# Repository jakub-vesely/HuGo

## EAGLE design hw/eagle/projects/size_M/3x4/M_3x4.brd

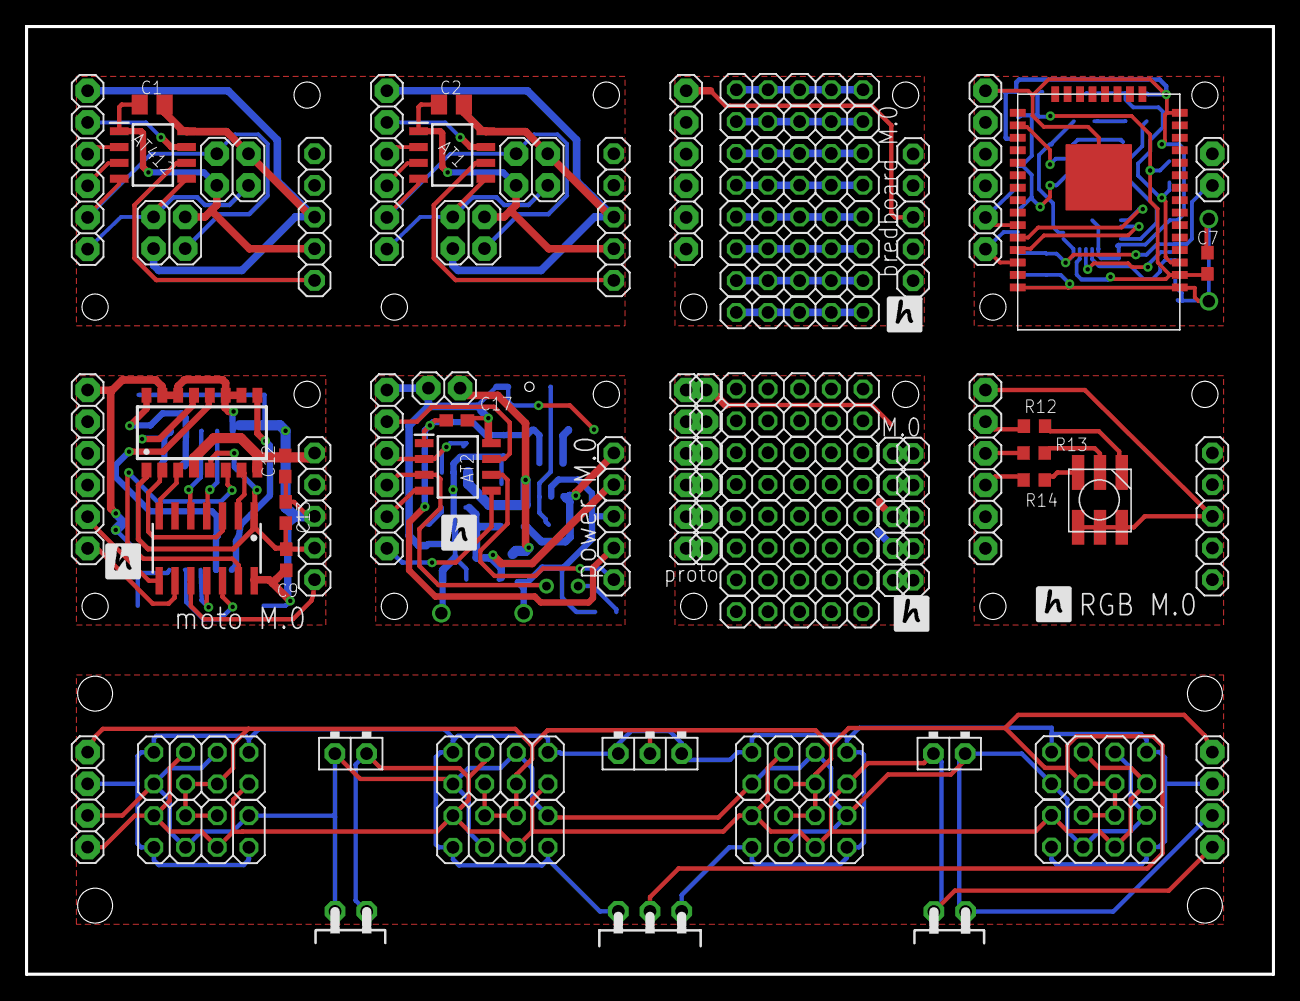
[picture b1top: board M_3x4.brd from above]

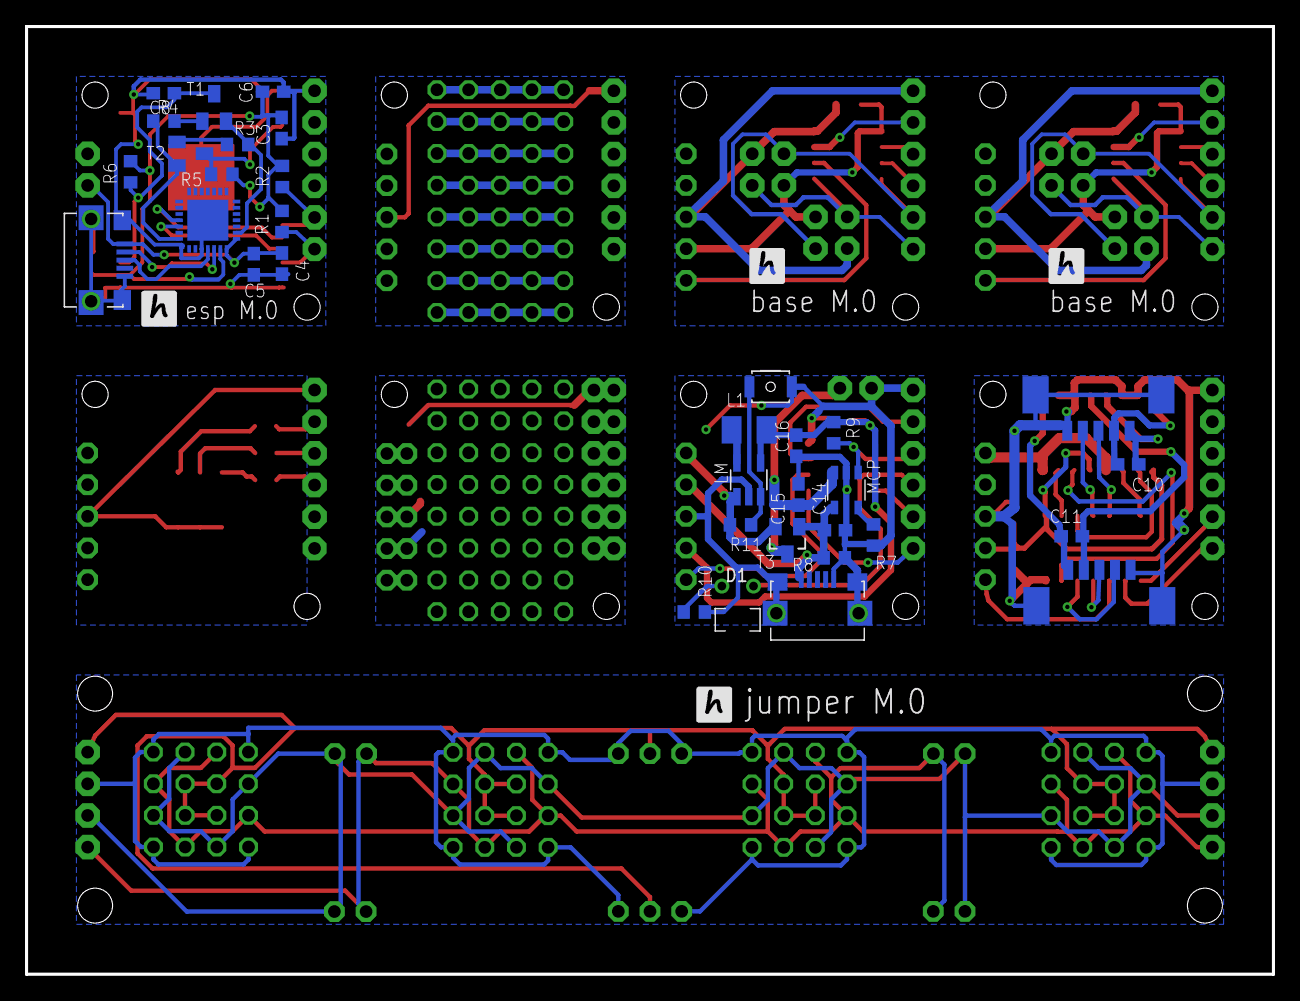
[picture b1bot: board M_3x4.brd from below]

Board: 2 copper layers, 100.0 x 76.0 mm, 106 parts (34 on the bottom side), 92 nets.

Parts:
AT1, AT2, AT412: AT412; SOIC127P600X175-8N
C1, C2: 100n; C0805K
C3, C4, C6, C9, C10, C11, C17: 100n; C0603
C5, C16: 10u; C0603
C7: 0.1F; C0603
C8: 2u2; C0603
C12, C13, C14, C15: 4u7; C0603
D1: LED1.8
IC1: CP2102; MLP28
IC2: AT414; SO14
JP1, JP2, JP9, JP10, JP13, JP15, JP17, JP19, JP21: 1X06
JP3, JP4, JP6, JP7: 2X02
JP5, JP8, JP11, JP14, JP16, JP18, JP20, JP22: 1X05
JP12: 1X02
JP23, JP25, JP26, JP27, JP28, JP29, JP33, JP34: 2X04
JP24, JP35: 1X02/90F
JP30, JP36: 1X02/90
JP31: 1X03/90
JP32: 1X03/90F
JP37, JP38: 1X04
L1: 2u2; L3230M
LIPOL: 1X02
LM: TC; SOT32-5
MCP: MCP; SOT23-5
MX1: MX1508; SOP16
R1, R2, R10: 2k2; R0603
R3, R4, R5, R6: 12k; R0603
R7: 22k; R0603
R8, R9, R11: 100k; R0603
R12, R13, R14: 330; R0603
RESET: BYTTON-B3U; BUTTON-B3U
T1, T2: SOT23-BEC
T3: FDV; SOT23
U$1, U$2, U$3, U$4, U$5, U$6, U$7, U$8, U$11, U$12, U$13, U$14, U$15, U$16, U$17, U$18: PINHD-1X5_AUTO; 1X5_AUTO
U$9: TTGO-MICRO-32
U$10: A1250WR
U$19: RGB_WW-FCE50TC-Q1
USB, USB1: MICRO-USB
X22: A1250WR

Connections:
FOTO1: IC2.5, U$10.3
FOTO2: IC2.12, X22.4
GND: AT1.8, AT412.8, C1.2, C2.2, JP1.6, JP2.6, JP3.4, JP4.1, JP5.3, JP6.4, JP7.1, JP8.3
GND1: JP9.6, JP11.3
GND2: C3.2, C4.1, C5.1, C6.2, C7.2, C8.2, IC1.3, IC1.EXP, IC1.M, JP10.6, U$9.GND1, U$9.GND2, U$9.GND3, U$9.GND4, USB.GND, USB.GND1, USB.GND2, USB.GND3, USB.GND4, USB.P$1, USB.P$2
GND3: C9.1, C12.1, C13.1, IC2.14, JP13.6, JP14.3, MX1.10, MX1.11, MX1.14, MX1.15, U$10.5, U$10.$1, U$10.$2, X22.5, X22.$1, X22.$2
GND4: AT2.8, C14.1, C15.1, C16.1, C17.2, JP15.6, JP16.3, LIPOL.1, LM.GND, MCP.2, R7.1, R8.1, R10.1, RESET.P$2, USB1.GND, USB1.GND1, USB1.GND2, USB1.GND3, USB1.GND4, USB1.P$1, USB1.P$2
GND5: JP17.6, JP18.3, JP19.6, JP20.3
GND6: JP21.6, JP22.3, U$19.4, U$19.5, U$19.6
GND7: JP23.1, JP23.7, JP25.2, JP25.8, JP26.1, JP26.7, JP27.2, JP27.8, JP28.1, JP28.7, JP29.2, JP29.8, JP31.1, JP31.3, JP32.1, JP32.3, JP33.1, JP33.7, JP34.2, JP34.8, JP37.2, JP38.3
INA1: IC2.3, MX1.2
INA2: IC2.13, MX1.6
INB1: IC2.7, MX1.3
INB2: IC2.2, MX1.7
LED1: IC2.4, U$10.4
LED2: IC2.11, X22.3
M1: C10.2, MX1.13, U$10.1
M2: C10.1, MX1.16, U$10.2
M3: C11.2, MX1.9, X22.1
M4: C11.1, MX1.12, X22.2
M_SRC: C12.2, JP14.1, MX1.4, MX1.8
unnamed: U$1.1, U$1.2, U$1.3, U$1.4, U$1.5
unnamed: U$2.1, U$2.2, U$2.3, U$2.4, U$2.5
unnamed: U$3.1, U$3.2, U$3.3, U$3.4, U$3.5
unnamed: U$4.1, U$4.2, U$4.3, U$4.4, U$4.5
unnamed: U$5.1, U$5.2, U$5.3, U$5.4, U$5.5
unnamed: U$6.1, U$6.2, U$6.3, U$6.4, U$6.5
unnamed: U$7.1, U$7.2, U$7.3, U$7.4, U$7.5
unnamed: U$8.1, U$8.2, U$8.3, U$8.4, U$8.5
unnamed: IC1.5, USB.D-
unnamed: IC1.4, USB.D+
unnamed: IC1.25, U$9.RXD0
unnamed: IC1.26, U$9.TXD0
unnamed: R4.2, T1.B
unnamed: R3.2, T2.B
unnamed: IC1.9, R3.1, T1.E
unnamed: IC1.28, R4.1, T2.E
unnamed: R5.1, T2.C, U$9.IO0
unnamed: C8.1, R6.2, T1.C, U$9.EN
unnamed: IC2.9, JP13.1
unnamed: IC2.8, JP13.2
unnamed: IC2.10, JP14.5
unnamed: C15.2, LIPOL.2, MCP.3, T3.D
unnamed: C14.2, JP16.2, MCP.4, R8.2, T3.G, USB1.VUSB
unnamed: MCP.5, R7.2
unnamed: JP16.1, LM.VIN, R11.1, T3.S
unnamed: D1.K, R10.2
unnamed: LM.SHDN, R11.2, RESET.P$1
unnamed: L1.1, LM.VOUT
unnamed: JP17.5, JP19.5
unnamed: JP17.4, JP19.4
unnamed: JP17.3, JP19.3
unnamed: JP17.2, JP19.2
unnamed: JP17.1, JP19.1
unnamed: JP18.5, JP20.5
unnamed: JP18.2, JP20.2
unnamed: JP18.1, JP20.1
unnamed: R13.2, U$19.2
unnamed: R12.2, U$19.1
unnamed: R14.2, U$19.3
unnamed: JP21.5, R12.1
unnamed: JP21.4, R13.1
unnamed: JP21.3, R14.1
PA1: AT1.7, JP1.5
PA2: AT1.2, JP1.4
PA3: AT412.7, JP2.5
PA4: AT1.3, JP1.3
PA5: AT2.7, JP15.5
PA6: AT412.2, JP2.4
PA7: AT412.3, JP2.3
PA8: AT2.2, JP15.4, MCP.1, R9.2
PA9: AT2.3, D1.A, JP15.3
SCL: AT412.5, JP2.1, JP3.3, JP4.2
SCL1: AT1.5, JP1.1, JP6.3, JP7.2
SCL2: JP10.1, R1.1, U$9.IO22
SCL3: AT2.5, JP15.1
SCL4: JP23.2, JP23.5, JP24.1, JP25.4, JP25.7, JP26.2, JP26.5, JP27.4, JP27.7, JP28.2, JP28.5, JP29.4, JP29.7, JP30.2, JP33.2, JP33.5, JP34.4, JP34.7, JP35.2, JP36.1, JP37.4, JP38.1
SDA: AT412.4, JP2.2, JP3.2, JP4.3
SDA1: AT1.4, JP1.2, JP6.2, JP7.3
SDA2: JP10.2, R2.1, U$9.IO21
SDA3: AT2.4, JP15.2
SDA4: JP23.3, JP23.8, JP24.2, JP25.1, JP25.6, JP26.3, JP26.8, JP27.1, JP27.6, JP28.3, JP28.8, JP29.1, JP29.6, JP30.1, JP33.3, JP33.8, JP34.1, JP34.6, JP35.1, JP36.2, JP37.3, JP38.2
UPDI: AT412.6, JP5.5
UPDI1: AT1.6, JP8.5
UPDI2: AT2.6, JP16.5
VCC: C9.2, C13.2, IC2.1, JP14.4, MX1.1, MX1.5
VCC1: JP23.4, JP23.6, JP25.3, JP25.5, JP26.4, JP26.6, JP27.3, JP27.5, JP28.4, JP28.6, JP29.3, JP29.5, JP31.2, JP32.2, JP33.4, JP33.6, JP34.3, JP34.5, JP37.1, JP38.4
VDD: AT1.1, AT412.1, C1.1, C2.1, JP3.1, JP4.4, JP5.4, JP6.1, JP7.4, JP8.4
VDD2: C3.1, C6.1, C7.1, IC1.6, R1.2, R2.2, R5.2, R6.1, U$9.3V3
VDD3: AT2.1, C16.2, C17.1, JP16.4, L1.2, LM.BP, R9.1
VDD4: JP18.4, JP20.4
VUSB: C4.2, C5.2, IC1.7, IC1.8, JP12.2, USB.VUSB

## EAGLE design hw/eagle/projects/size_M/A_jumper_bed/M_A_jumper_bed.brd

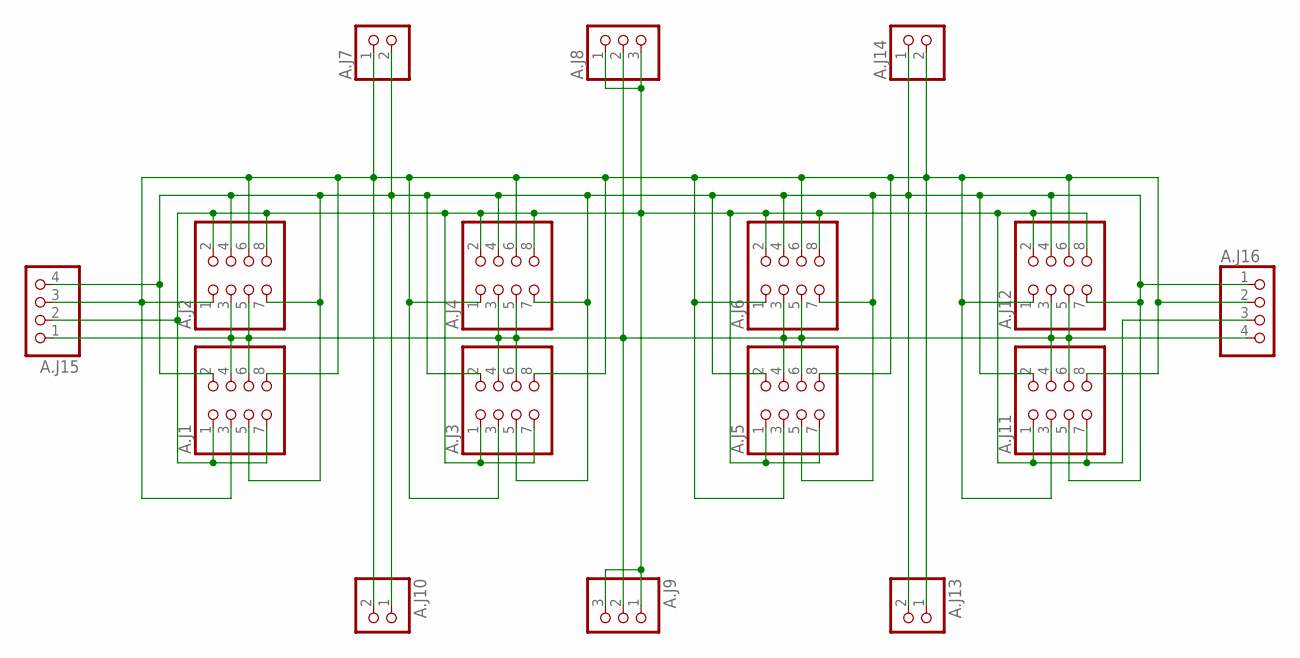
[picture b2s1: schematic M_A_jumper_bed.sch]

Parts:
A.J1, A.J2, A.J3, A.J4, A.J5, A.J6, A.J11, A.J12: PINHD-2X4; 2X04
A.J7, A.J14: PINHD-1X2/90; 1X02/90
A.J8: PINHD-1X3/90; 1X03/90
A.J9: PINHD-1X31X03/90F; 1X03/90F
A.J10, A.J13: PINHD-1X21X02/90F; 1X02/90F
A.J15, A.J16: PINHD-1X4; 1X04

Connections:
GND: A.J1.1, A.J1.7, A.J2.2, A.J2.8, A.J3.1, A.J3.7, A.J4.2, A.J4.8, A.J5.1, A.J5.7, A.J6.2, A.J6.8, A.J8.1, A.J8.3, A.J9.1, A.J9.3, A.J11.1, A.J11.7, A.J12.2, A.J12.8, A.J15.2, A.J16.3
SCL: A.J1.2, A.J1.5, A.J2.4, A.J2.7, A.J3.2, A.J3.5, A.J4.4, A.J4.7, A.J5.2, A.J5.5, A.J6.4, A.J6.7, A.J7.2, A.J10.1, A.J11.2, A.J11.5, A.J12.4, A.J12.7, A.J13.2, A.J14.1, A.J15.4, A.J16.1
SDA: A.J1.3, A.J1.8, A.J2.1, A.J2.6, A.J3.3, A.J3.8, A.J4.1, A.J4.6, A.J5.3, A.J5.8, A.J6.1, A.J6.6, A.J7.1, A.J10.2, A.J11.3, A.J11.8, A.J12.1, A.J12.6, A.J13.1, A.J14.2, A.J15.3, A.J16.2
VCC: A.J1.4, A.J1.6, A.J2.3, A.J2.5, A.J3.4, A.J3.6, A.J4.3, A.J4.5, A.J5.4, A.J5.6, A.J6.3, A.J6.5, A.J8.2, A.J9.2, A.J11.4, A.J11.6, A.J12.3, A.J12.5, A.J15.1, A.J16.4

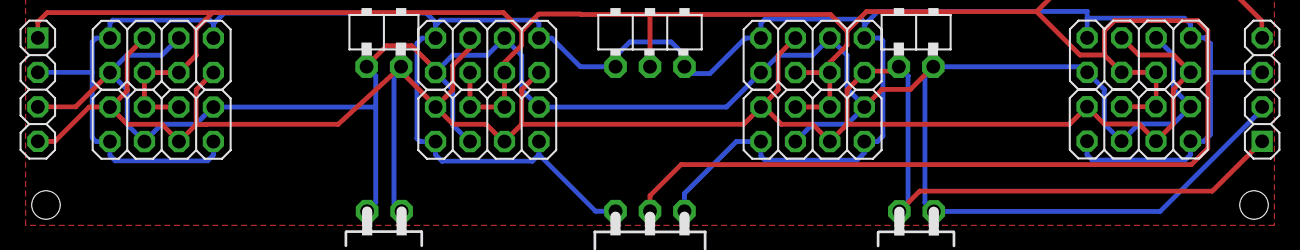
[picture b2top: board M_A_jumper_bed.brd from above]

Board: 2 copper layers, 16 parts (0 on the bottom side), 4 nets.

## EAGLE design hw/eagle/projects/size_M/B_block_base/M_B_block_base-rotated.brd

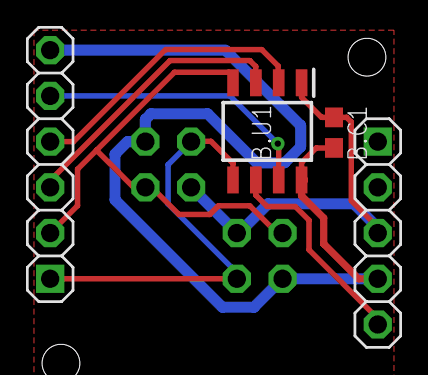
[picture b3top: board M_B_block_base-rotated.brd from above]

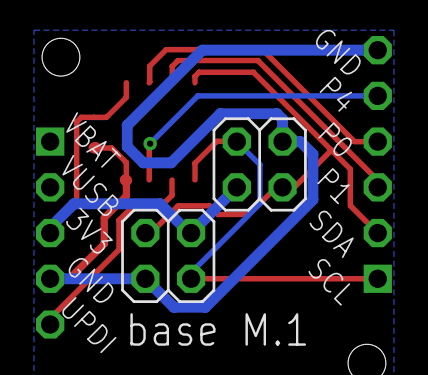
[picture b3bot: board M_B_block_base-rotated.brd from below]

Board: 2 copper layers, 6 parts (2 on the bottom side), 8 nets.

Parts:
B.C1: 100n; C0603
B.J2: 1X06
B.J4: 2X02
B.J5: 1X05
B.U1: AT412; SOIC127P600X175-8N
JB3: 2X02

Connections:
3V3: B.C1.1, B.J4.4, B.J5.3, B.U1.1, JB3.1
GND: B.C1.2, B.J2.6, B.J4.1, B.J5.4, B.U1.8, JB3.4
PA3: B.J2.5, B.U1.7
PA6: B.J2.4, B.U1.2
PA7: B.J2.3, B.U1.3
SCL: B.J2.1, B.J4.3, B.U1.5, JB3.2
SDA: B.J2.2, B.J4.2, B.U1.4, JB3.3
UPDI: B.J5.5, B.U1.6

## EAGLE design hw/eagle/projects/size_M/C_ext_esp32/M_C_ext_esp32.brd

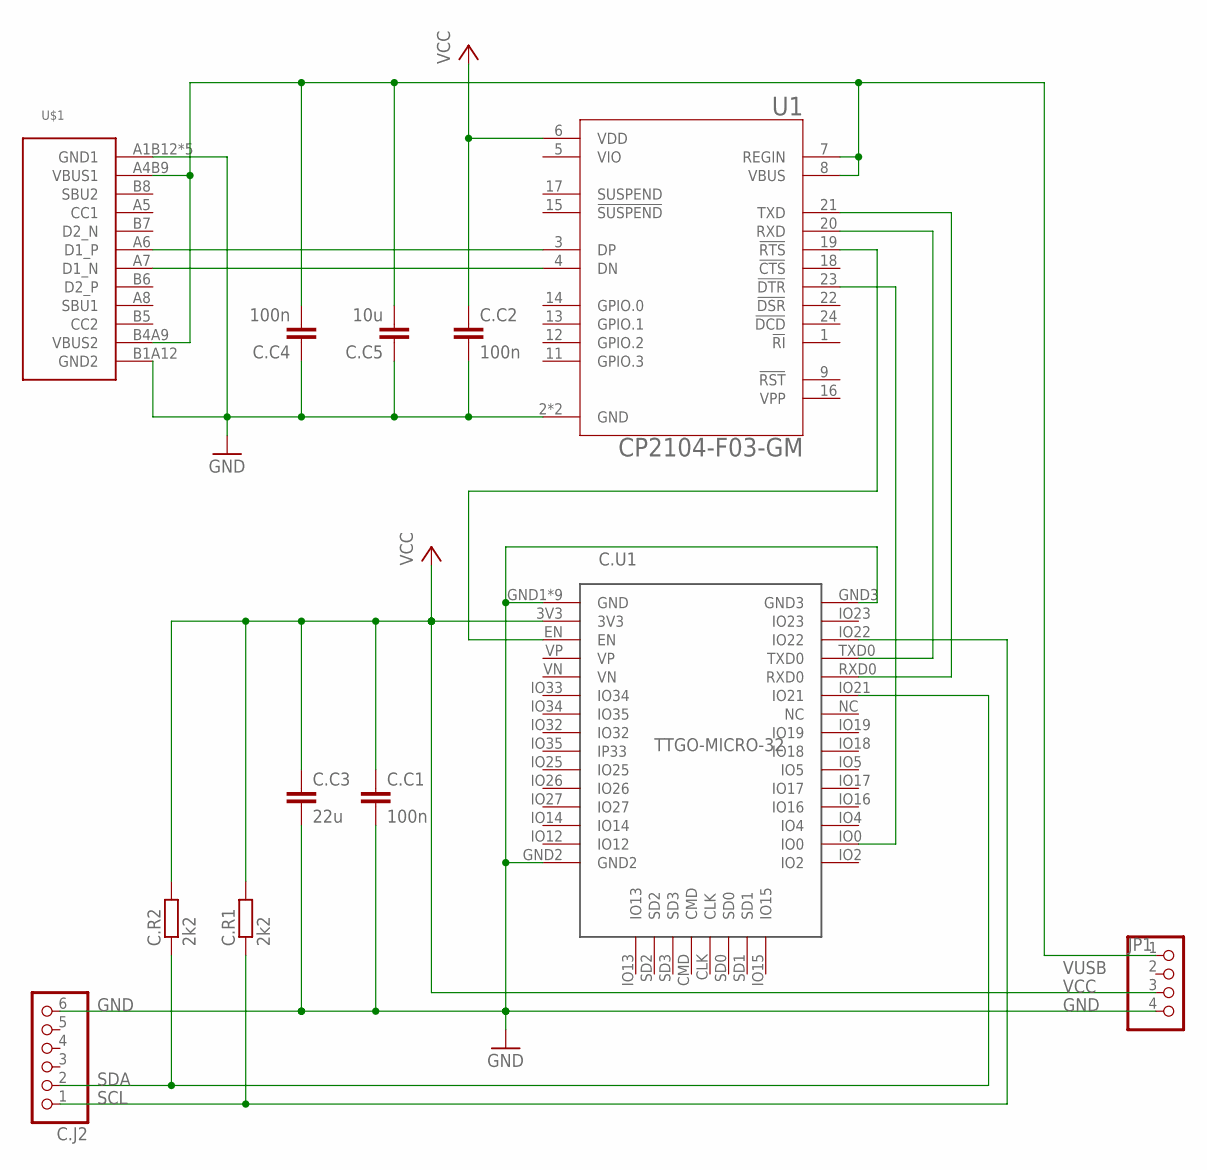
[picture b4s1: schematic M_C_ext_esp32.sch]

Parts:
C.C1, C.C2, C.C4: 100n; C0603
C.C3: 22u; C0805
C.C5: 10u; C0603
C.J2: PINHD-1X6; 1X06
C.R1, C.R2: 2k2; R0603
C.U1: TTGO-MICRO-32
JP1: PINHD-1X4; 1X04
U1: CP2104-F03-GM; QFN50P400X400X80-25N
U$1: USB-C

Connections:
GND: C.C1.2, C.C2.2, C.C3.2, C.C4.1, C.C5.1, C.J2.6, C.U1.GND1 (GND), C.U1.GND2, C.U1.GND3, C.U1.GND4 (GND), C.U1.GND5 (GND), C.U1.GND6 (GND), C.U1.GND7 (GND), C.U1.GND8 (GND), C.U1.GND9 (GND), C.U1.GND10 (GND), C.U1.GND11 (GND), JP1.4, U1.2 (GND), U1.25 (GND), U$1.A1B12 (GND1), U$1.B1A12 (GND2), U$1.SH1 (GND1), U$1.SH2 (GND1), U$1.SH3 (GND1), U$1.SH4 (GND1)
unnamed: U1.4 (DN), U$1.A7 (D1_N)
unnamed: U1.3 (DP), U$1.A6 (D1_P)
PROG: C.U1.IO0, U1.23 (!DTR)
RESET: C.U1.EN, U1.19 (!RTS)
RX: C.U1.TXD0, U1.20 (RXD)
SCL: C.J2.1, C.R1.1, C.U1.IO22
SDA: C.J2.2, C.R2.1, C.U1.IO21
TX: C.U1.RXD0, U1.21 (TXD)
VCC: C.C1.1, C.C2.1, C.C3.1, C.R1.2, C.R2.2, C.U1.3V3, JP1.3, U1.6 (VDD)
VIO: U1.5 (VIO)
VUSB: C.C4.2, C.C5.2, JP1.1, U1.7 (REGIN), U1.8 (VBUS), U$1.A4B9 (VBUS1), U$1.B4A9 (VBUS2)

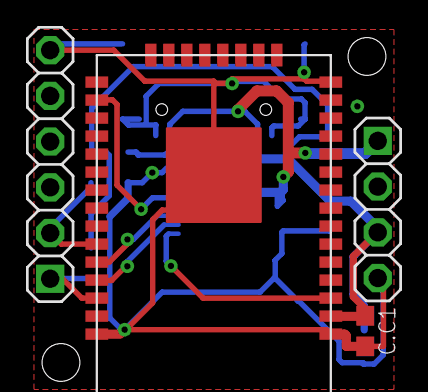
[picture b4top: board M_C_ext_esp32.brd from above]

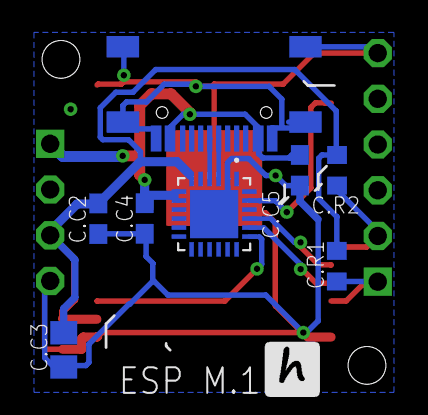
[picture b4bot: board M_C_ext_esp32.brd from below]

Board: 2 copper layers, 12 parts (8 on the bottom side), 11 nets.

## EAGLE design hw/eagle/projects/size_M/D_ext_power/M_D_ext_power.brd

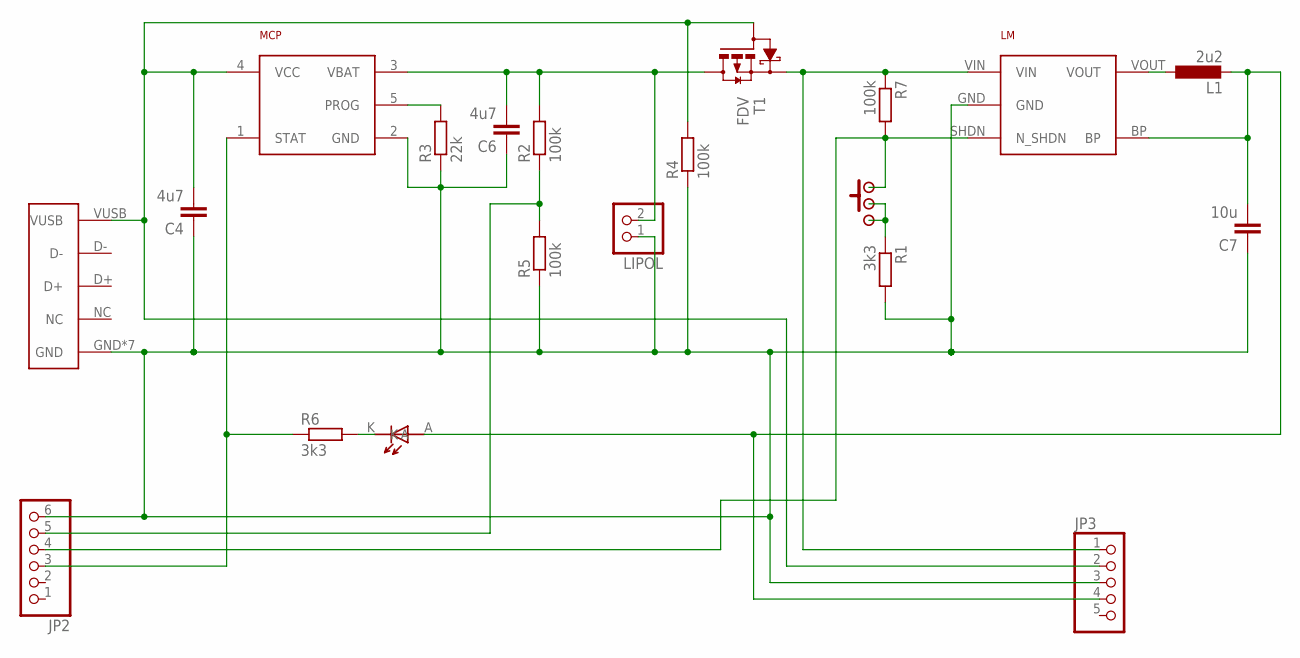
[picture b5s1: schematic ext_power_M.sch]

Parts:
C4, C6: 4u7; C0603
C7: 10u; C0603
D1: LED1.8
JP2: PINHD-1X6; 1X06
JP3: PINHD-1X5; 1X05
L1: 2u2; L3230M
LIPOL: PINHD-1X2; 1X02
LM: TC; SOT32-5
MCP: MCP; SOT23-5
ON/OFF/RESET: SWITCH
R1, R6: 3k3; R0603
R2, R4, R5, R7: 100k; R0603
R3: 22k; R0603
T1: FDV; SOT23
USB: MICRO-USB

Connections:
GND: C4.1, C6.1, C7.1, JP2.6, JP3.3, LIPOL.1, LM.GND, MCP.2 (GND), R1.2, R3.1, R4.1, R5.1, USB.GND, USB.GND1 (GND), USB.GND2 (GND), USB.GND3 (GND), USB.GND4 (GND), USB.P$1 (GND), USB.P$2 (GND)
unnamed: ON/OFF/RESET.P$2, ON/OFF/RESET.P$3, ON/OFF/RESET.P$5, R1.1
unnamed: L1.1, LM.VOUT
unnamed: D1.K, R6.2
unnamed: JP2.5, R2.1, R5.2
unnamed: C6.2, LIPOL.2, MCP.3 (VBAT), R2.2, T1.D
unnamed: C4.2, JP3.2, MCP.4 (VCC), R4.2, T1.G, USB.VUSB
unnamed: MCP.5 (PROG), R3.2
unnamed: JP3.1, LM.VIN, R7.1, T1.S
unnamed: JP2.4, LM.SHDN (N_SHDN), ON/OFF/RESET.P$1, ON/OFF/RESET.P$4, R7.2
PA7: JP2.3, MCP.1 (STAT), R6.1
VDD: C7.2, D1.A, JP3.4, L1.2, LM.BP

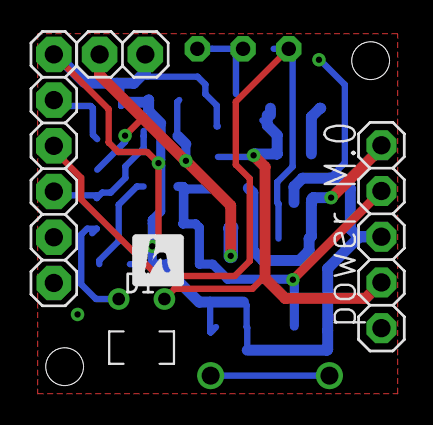
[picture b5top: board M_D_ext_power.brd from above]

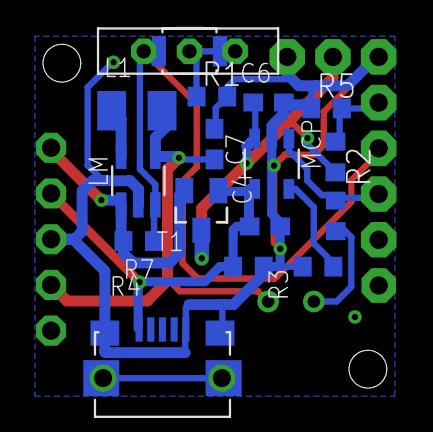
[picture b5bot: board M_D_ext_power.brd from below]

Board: 2 copper layers, 20 parts (16 on the bottom side), 12 nets.

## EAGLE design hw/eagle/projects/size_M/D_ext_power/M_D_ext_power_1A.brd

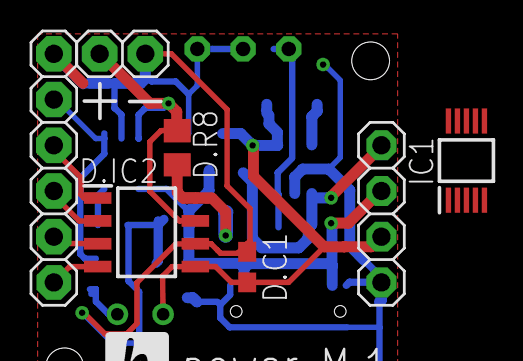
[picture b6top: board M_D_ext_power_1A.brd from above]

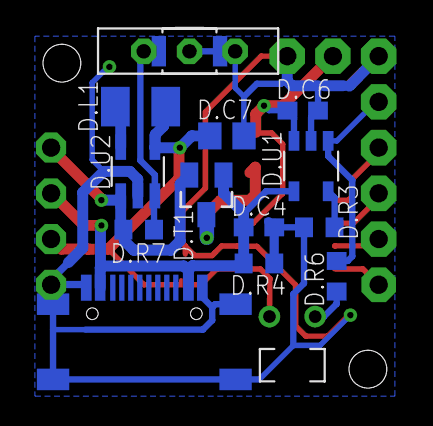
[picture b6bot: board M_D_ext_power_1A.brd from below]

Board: 2 copper layers, 21 parts (14 on the bottom side), 15 nets.

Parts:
D.C1: 100n; C0603
D.C4, D.C6: 4u7; C0603
D.C7: 22u; C0805
D.D1: LED_1.8
D.IC2: INA219AIDR; SOIC127P600X175-8N
D.J2: 1X06
D.J3: 1X04
D.L1: 2u2; L3230M
D.LIPOL: 1X02
D.ON/OFF/RESET: SWITCH
D.R3: 12k; R0603
D.R4, D.R7: 100k; R0603
D.R6: 2k2; R0603
D.R8: 0.1; R0805
D.T1: FDV; SOT23
D.U1: MCP; SOT23-5
D.U2: TC; SOT32-5
IC1: MCP73833-AMI_UN; SOP50P490X110-10N
U$1: USB-C

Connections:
GND: D.C1.1, D.C4.1, D.C6.1, D.C7.1, D.IC2.6, D.J2.6, D.J3.4, D.LIPOL.1, D.ON/OFF/RESET.P$2, D.ON/OFF/RESET.P$3, D.ON/OFF/RESET.P$5, D.R3.1, D.R4.1, D.U1.2, D.U2.GND, U$1.A1B12, U$1.B1A12, U$1.SH1, U$1.SH2, U$1.SH3, U$1.SH4
unnamed: D.IC2.1, D.J2.4
unnamed: D.L1.1, D.U2.VOUT
unnamed: D.D1.1, D.R6.2
unnamed: D.ON/OFF/RESET.P$1, D.ON/OFF/RESET.P$4, D.R7.2, D.U2.SHDN
unnamed: D.IC2.4, D.J2.1
unnamed: D.IC2.3, D.J2.2
unnamed: D.IC2.8, D.R8.1, D.T1.D
unnamed: D.C4.2, D.J3.2, D.R4.2, D.T1.G, D.U1.4, U$1.A4B9, U$1.B4A9
unnamed: D.IC2.2, D.J2.3
unnamed: D.R3.2, D.U1.5
unnamed: D.J3.1, D.R7.1, D.T1.S, D.U2.VIN
unnamed: D.C6.2, D.IC2.7, D.LIPOL.2, D.R8.2, D.U1.3
PA7: D.J2.5, D.R6.1, D.U1.1
VDD: D.C1.2, D.C7.2, D.D1.2, D.IC2.5, D.J3.3, D.L1.2, D.U2.BP

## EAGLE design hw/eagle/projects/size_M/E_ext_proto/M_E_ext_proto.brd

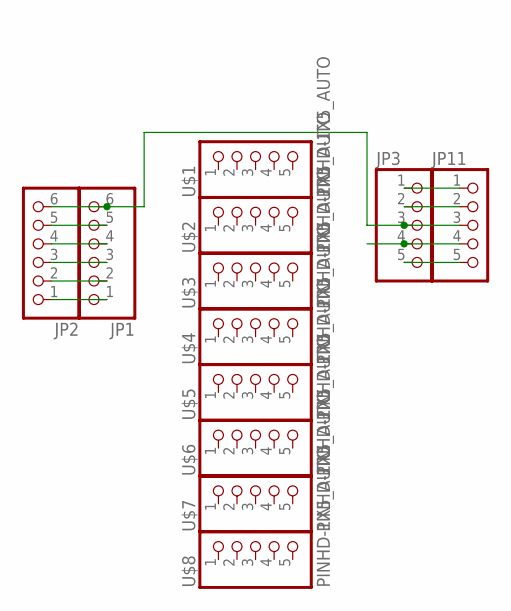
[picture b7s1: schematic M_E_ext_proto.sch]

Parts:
JP1, JP2: PINHD-1X6; 1X06
JP3, JP11: PINHD-1X5; 1X05
U$1, U$2, U$3, U$4, U$5, U$6, U$7, U$8: PINHD-1X5_AUTO; 1X5_AUTO

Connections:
GND: JP1.6, JP2.6, JP3.3, JP11.3
unnamed: JP1.5, JP2.5
unnamed: JP1.4, JP2.4
unnamed: JP1.3, JP2.3
unnamed: JP1.2, JP2.2
unnamed: JP1.1, JP2.1
unnamed: JP3.5, JP11.5
unnamed: JP3.2, JP11.2
unnamed: JP3.1, JP11.1
VDD: JP3.4, JP11.4

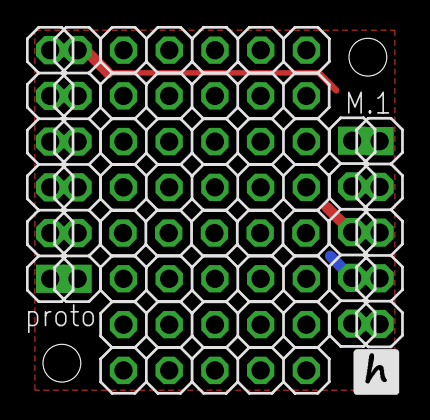
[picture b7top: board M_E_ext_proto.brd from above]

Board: 2 copper layers, 12 parts (0 on the bottom side), 10 nets.
